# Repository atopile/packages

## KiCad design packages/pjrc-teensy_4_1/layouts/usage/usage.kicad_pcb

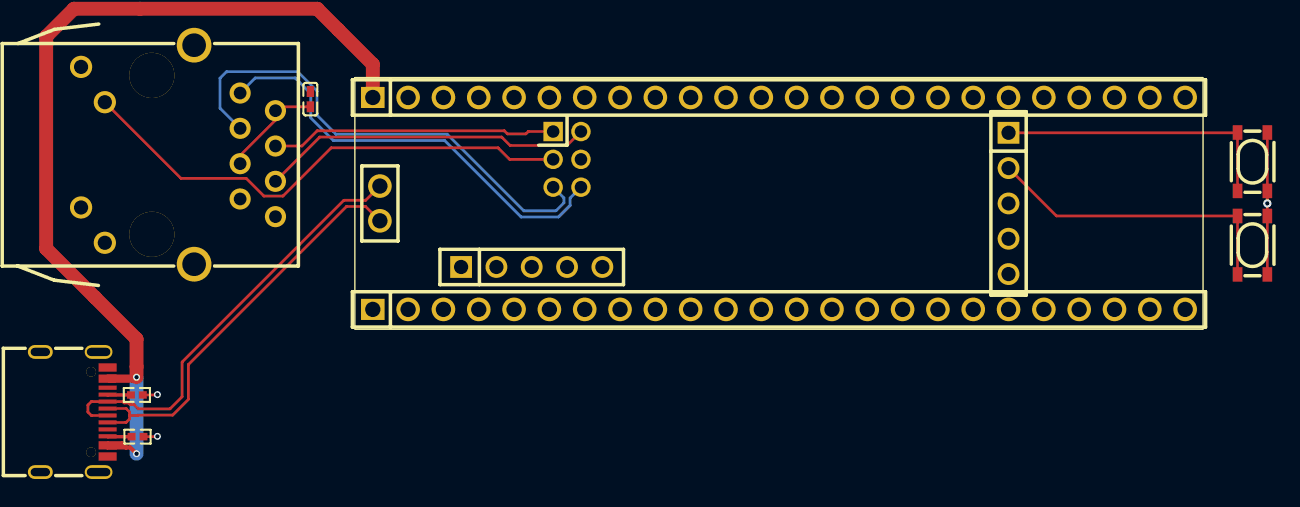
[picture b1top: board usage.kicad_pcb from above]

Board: 2 copper layers, 14 parts (0 on the bottom side), 15 nets.

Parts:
C1: 100nF ±10% 16V X7R; C0402
CN1: CONN-TH_2P-P2.50_YZ88715155P-02025-01
R1, R2: 4.7kΩ ±1% 62.5mW; R0402
RJ1: RJ45-TH_J1B1211CCD
SW1, SW2: KEY-SMD_4P-L4.2-W3.2-P2.20-LS4.6
U1: HDR-TH_6P-P2.00-V-F-R2-C3-S2.00
U2, U5: HDR-TH_5P-P2.54-V-F
U3, U4: HDR-TH_24P-P2.54-V-F
U6: PJRC_Teensy_4_1
USB1: USB-C-SMD_KH-TYPE-C-16P

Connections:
A5: R1.1, USB1.A5
B5: R2.1, USB1.B5
ETH_LED_SPEED: RJ1.10, U1.3
ETH_RX_N: RJ1.6, U1.2
ETH_RX_P: RJ1.4, U1.1
ETH_TX_N: RJ1.3, U1.5
ETH_TX_P: RJ1.1, U1.6
GND: C1.1, R1.2, R2.2, RJ1.8, RJ1.9, RJ1.13, RJ1.14, SW1.3, SW1.4, SW2.3, SW2.4, U1.4, U2.3, U3.1, U4.2, U4.15, U5.4, U5.5, USB1.1, USB1.2, USB1.3, USB1.4, USB1.A1, USB1.A12, USB1.B1, USB1.B12
USB_N: CN1.1, USB1.A7, USB1.B7
USB_P: CN1.2, USB1.A6, USB1.B6
_2: C1.2, RJ1.2, RJ1.5
on_off-input: SW1.1, SW1.2, U2.1
power-VCC: U4.1, USB1.A4, USB1.A9, USB1.B4, USB1.B9
power_3v3-VCC: U2.4, U3.15, U4.3
program-input: SW2.1, SW2.2, U2.2
